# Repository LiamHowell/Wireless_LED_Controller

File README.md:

# Wireless_LED_Controller

<h2> Attributions </h2>

Many thanks to [Robert](https://forum.core-electronics.com.au/u/robert93820) from the Core Electronics forum, he has been a huge help to both myself and the community

Progress was tracked on the [Core Electronics Maker Forum](https://forum.core-electronics.com.au/t/12-day-project-esp32-led-controller/12926)

I'll eventually circle back to this project in a more wholistic sense so that its super simple to use.

If you have any questions send them through!

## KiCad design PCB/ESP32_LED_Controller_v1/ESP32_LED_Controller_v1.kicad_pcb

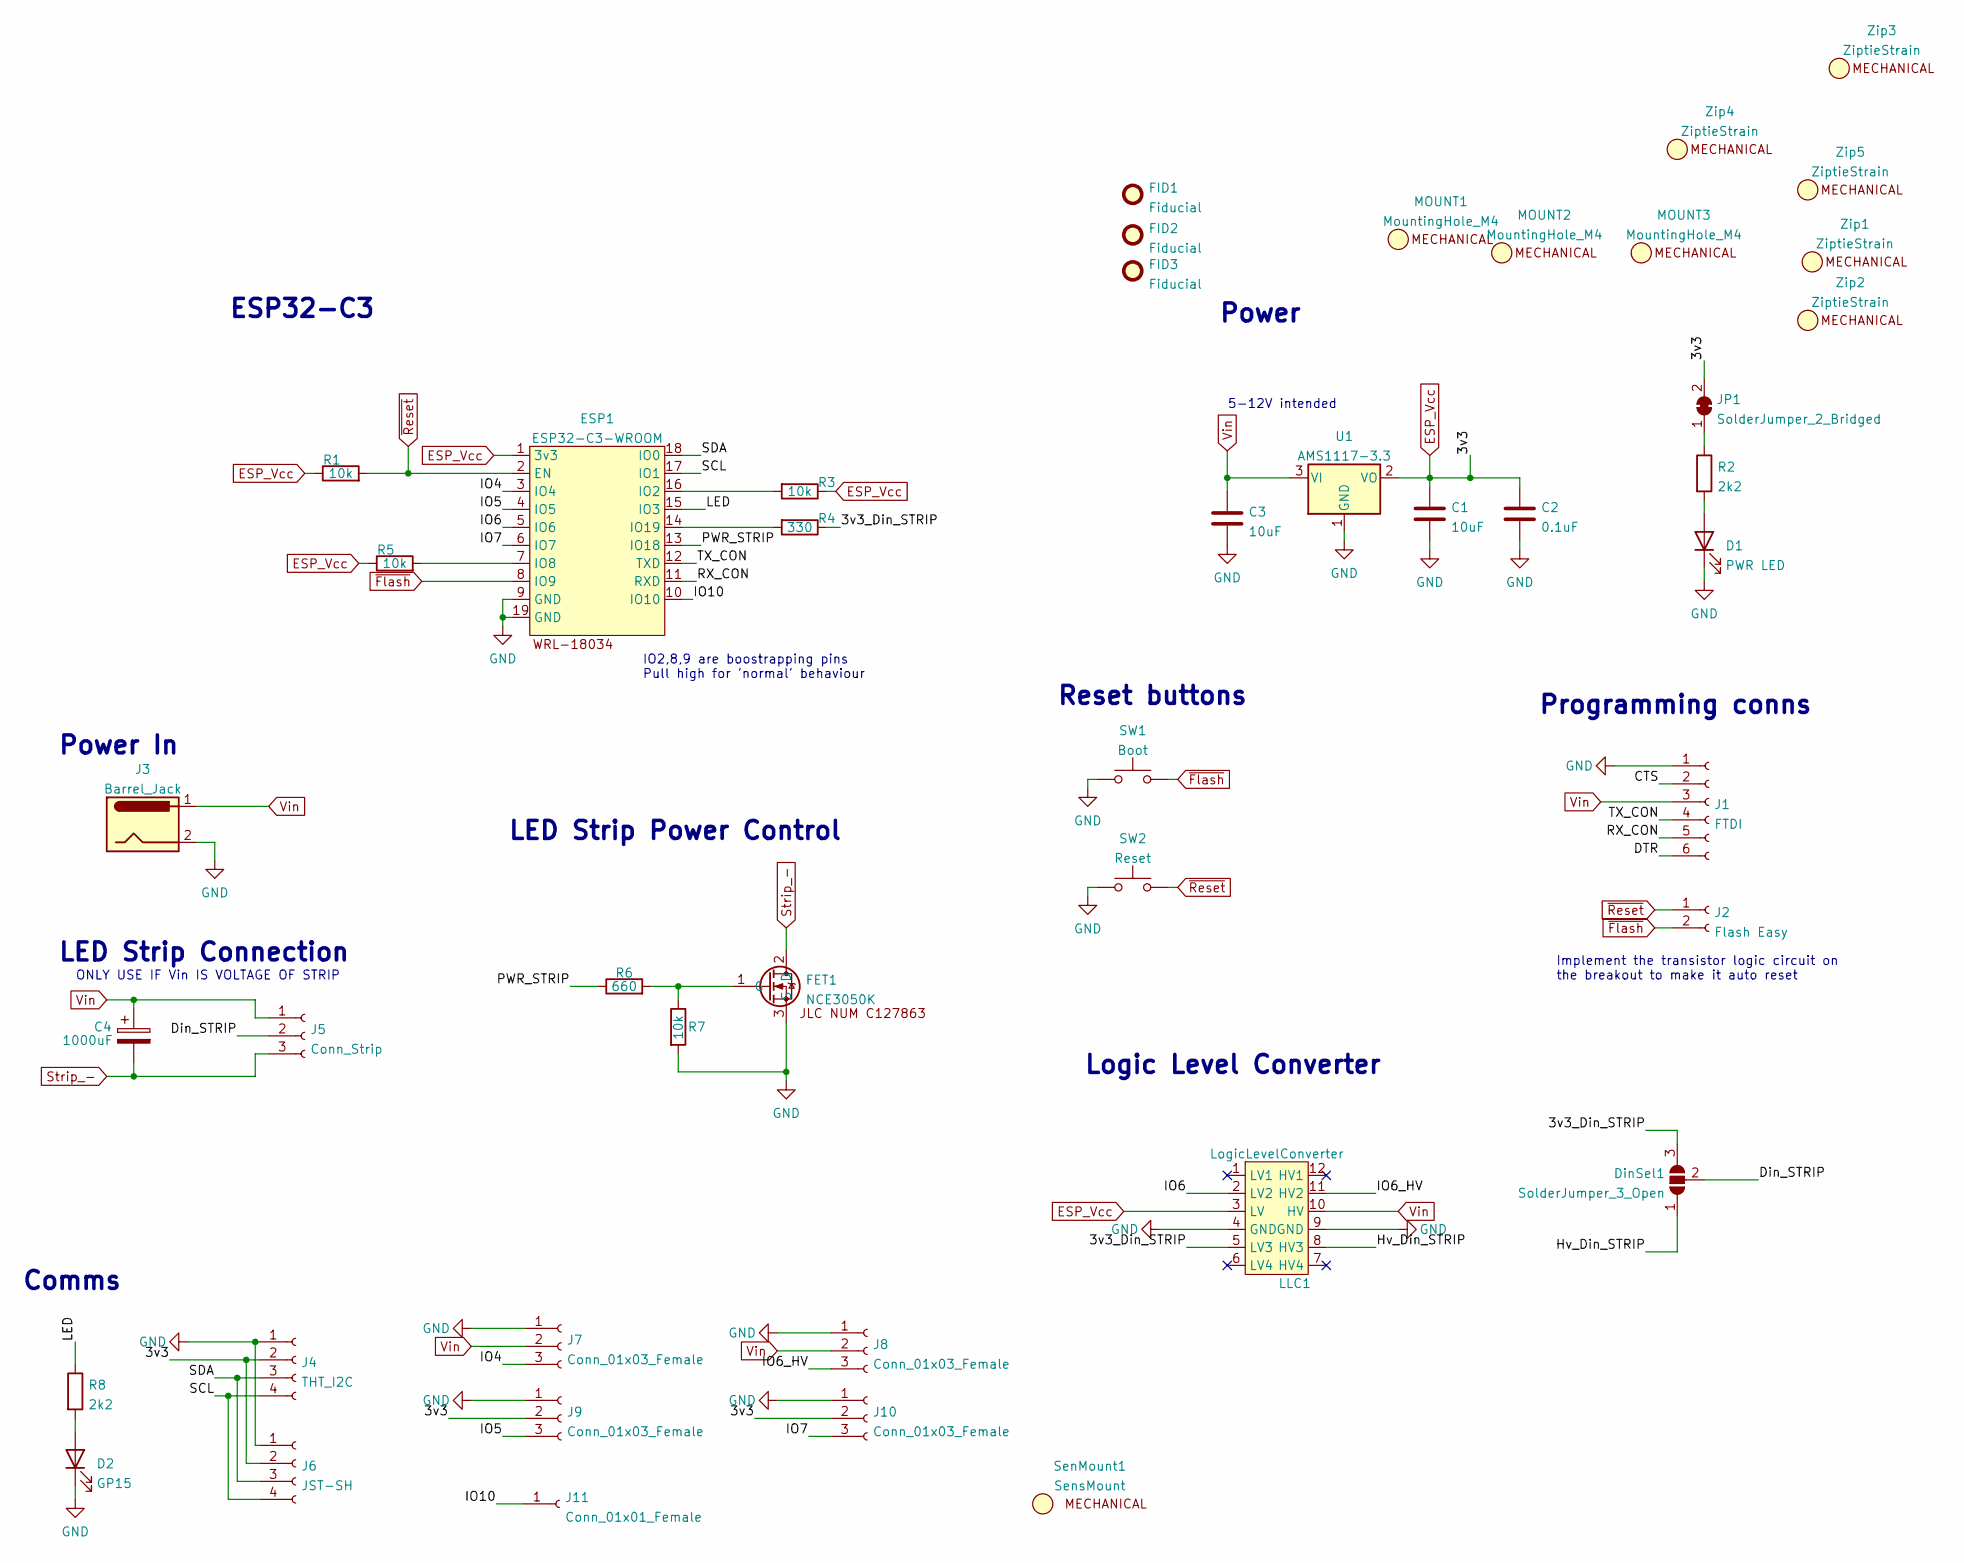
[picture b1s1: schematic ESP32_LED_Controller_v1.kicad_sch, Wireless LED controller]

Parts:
C1, C3: 10uF; C_0603_1608Metric_Pad1.08x0.95mm_HandSolder
C2: 0.1uF; C_0603_1608Metric_Pad1.08x0.95mm_HandSolder
C4: 1000uF; CP_Radial_D10.0mm_P5.00mm
D1: PWR LED; LED_0603_1608Metric_Pad1.05x0.95mm_HandSolder
D2: GP15; LED_0603_1608Metric_Pad1.05x0.95mm_HandSolder
DinSel1: SolderJumper_3_Open; SolderJumper-3_P1.3mm_Open_Pad1.0x1.5mm
ESP1: ESP32-C3-WROOM; ESP32-C3
FET1: NCE3050K; TO-252-2
FID1, FID2, FID3: Fiducial; Fiducial_0.75mm_Mask1.5mm
J1: FTDI; PinHeader_1x06_P2.54mm_Vertical
J2: Flash Easy; PinHeader_1x02_P2.54mm_Vertical
J3: Barrel_Jack; BarrelJack
J4: THT_I2C; PinHeader_1x04_P2.54mm_Vertical
J5: Conn_Strip; Screw3Pin
J6: JST-SH; JST_SH_BM04B-SRSS-TB_1x04-1MP_P1.00mm_Vertical
J7, J9: Conn_01x03_Female; PinHeader_1x03_P2.54mm_Vertical
J8, J10: Conn_01x03_Female; Conn1x3SMD
J11: Conn_01x01_Female; Conn1x1SMD
JP1: SolderJumper_2_Bridged; SolderJumper-2_P1.3mm_Bridged_RoundedPad1.0x1.5mm
LLC1: LogicLevelConverter
MOUNT1, MOUNT2, MOUNT3: MountingHole_M4; MountingHole_4.3mm_M4
R1, R3, R5, R7: 10k; R_0603_1608Metric_Pad0.98x0.95mm_HandSolder
R2, R8: 2k2; R_0603_1608Metric_Pad0.98x0.95mm_HandSolder
R4: 330; R_0603_1608Metric_Pad0.98x0.95mm_HandSolder
R6: 660; R_0603_1608Metric_Pad0.98x0.95mm_HandSolder
SW1: Boot; Button
SW2: Reset; Button
SenMount1: SensMount; SensorMount_Double
U1: AMS1117-3.3; SOT-223-3_TabPin2
Zip1, Zip2, Zip3, Zip4, Zip5: ZiptieStrain; ZipTie_5x2

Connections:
/3v3_Din_STRIP: DinSel1.3 (B), LLC1.5 (LV3), R4.1
/CTS: J1.2
/DTR: J1.6
/Din_STRIP: DinSel1.2 (C), J5.2
/Hv_Din_STRIP: DinSel1.1 (A), LLC1.8 (HV3)
/IO4: ESP1.3 (IO4), J7.3
/IO5: ESP1.4 (IO5), J9.3
/IO6: ESP1.5 (IO6), LLC1.2 (LV2)
/IO6_HV: J8.3, LLC1.11 (HV2)
/IO7: ESP1.6 (IO7), J10.3
/IO10: ESP1.10 (IO10), J11.1
/LED: ESP1.15 (IO3), R8.1
/PWR_STRIP: ESP1.13 (IO18), R6.1
/RX_CON: ESP1.11 (RXD), J1.5
/SCL: ESP1.17 (IO1), J4.4, J6.4
/SDA: ESP1.18 (IO0), J4.3, J6.3
/TX_CON: ESP1.12 (TXD), J1.4
ESP_Vcc: C1.1, C2.1, ESP1.1 (3v3), J4.2, J6.2, J9.2, J10.2, JP1.2 (B), LLC1.3 (LV), R1.1, R3.1, R5.1, U1.2 (VO)
GND: C1.2, C2.2, C3.2, D1.1 (K), D2.1 (K), ESP1.9 (GND), ESP1.19 (GND), FET1.3 (S), J1.1, J3.2, J4.1, J6.1, J7.1, J8.1, J9.1, J10.1, LLC1.4 (GND), LLC1.9 (GND), R7.2, SW1.1, SW2.1, U1.1 (GND)
unnamed: D1.2 (A), R2.2
unnamed: D2.2 (A), R8.2
unnamed: ESP1.7 (IO8), R5.2
unnamed: ESP1.14 (IO19), R4.2
unnamed: ESP1.16 (IO2), R3.2
unnamed: FET1.1 (G), R6.2, R7.1
unnamed: JP1.1 (A), R2.1
Strip_-: C4.2, FET1.2 (D), J5.3
Vin: C3.1, C4.1, J1.3, J3.1, J5.1, J7.2, J8.2, LLC1.10 (HV), U1.3 (VI)
~Flash: ESP1.8 (IO9), J2.2, SW1.2
~Reset: ESP1.2 (EN), J2.1, R1.2, SW2.2

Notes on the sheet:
LED Strip Connection
IO2,8,9 are boostrapping pins Pull high for 'normal' behaviour
Power
Power In
Implement the transistor logic circuit on the breakout to make it auto reset
Reset buttons
LED Strip Power Control
Comms
Logic Level Converter
ESP32-C3
ONLY USE IF Vin IS VOLTAGE OF STRIP
Programming conns
5-12V intended

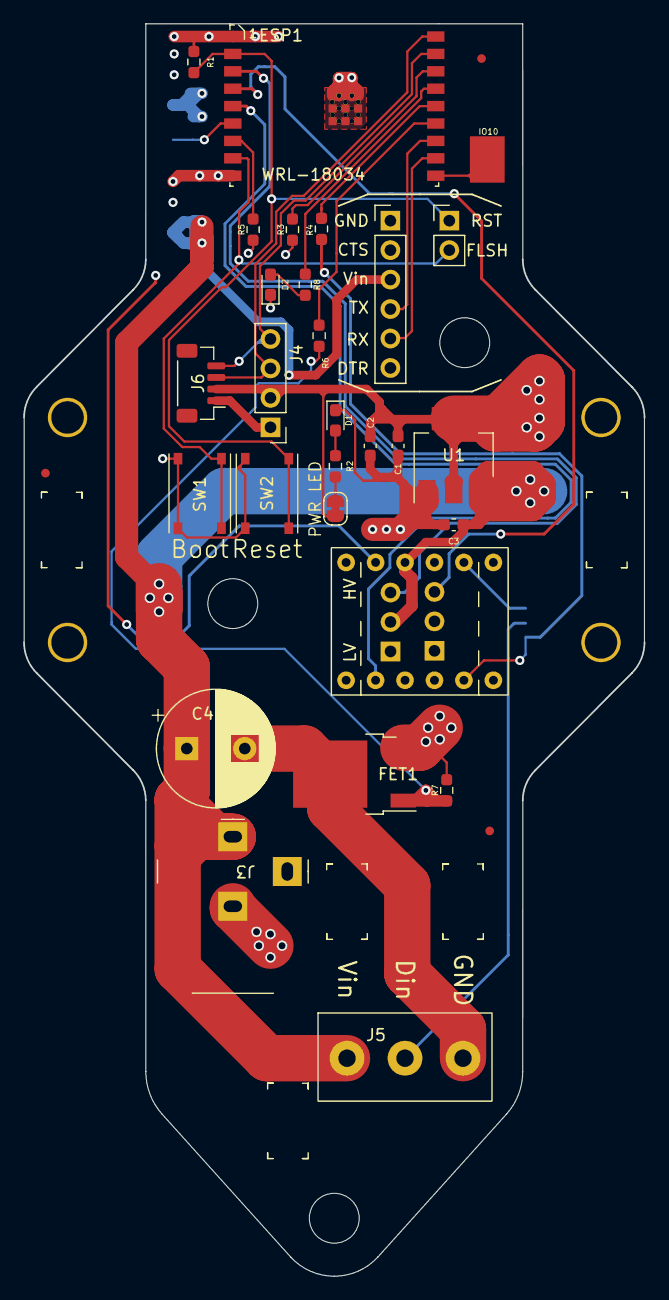
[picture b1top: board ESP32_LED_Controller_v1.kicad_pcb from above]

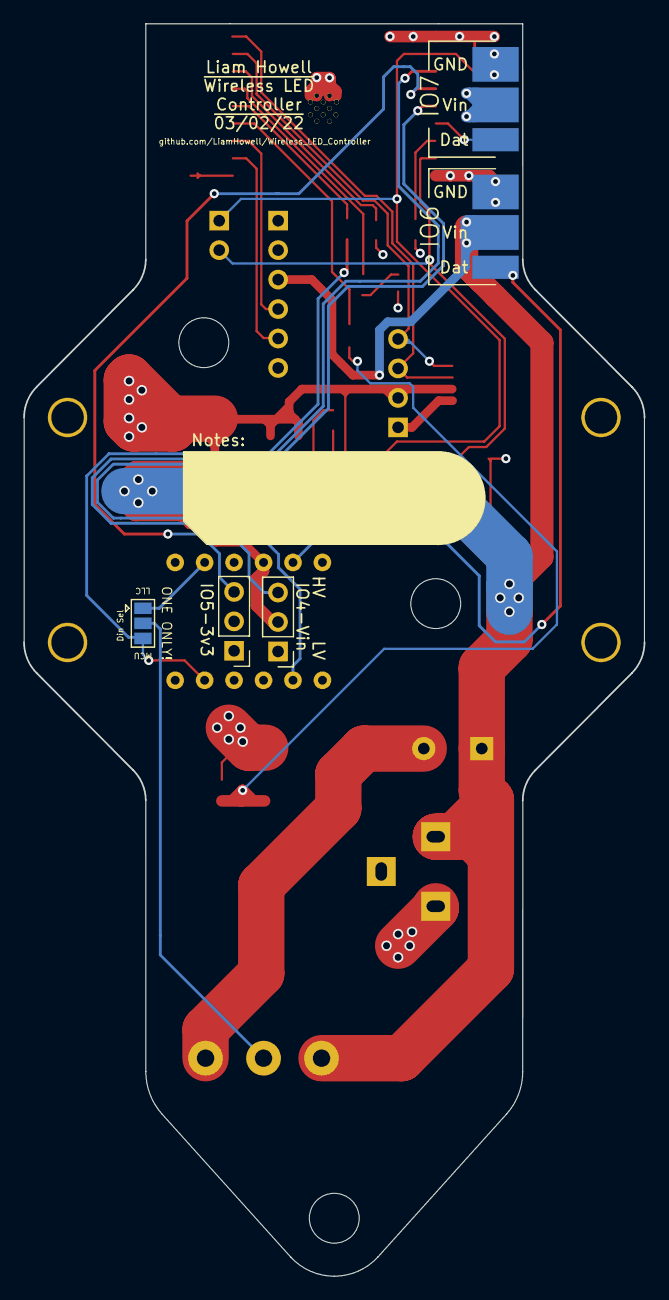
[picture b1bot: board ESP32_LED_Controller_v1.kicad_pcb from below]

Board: 4 copper layers, 53.5 x 108.0 mm, 45 parts (5 on the bottom side), 28 nets.

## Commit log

2022-01-27 Initial commit
    Kinda working code - it works but isnt super clean
2022-02-09 Adding PCB, napkin calcs
    Add extra testing code, PCB's
